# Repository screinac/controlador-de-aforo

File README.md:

# **Sistema Controlador de Aforo**

## Autores
- Oscar Leonardo Riveros Perez
- Sergio Camilo Reina Cardenas

Este repositorio de codigo esta destinado al desarrollo del proyecto de la asignatura Sistemas Embebidos de modo que a continuacion se mostrara todas las consideraciones, guias de diseño, codigo y pruebas para realizar el sistema de control de aforo planteado a continuacion.

## En que consiste el Controlador de Aforo?

El dispositivo consiste en un sistema embebido capaz de detectar la entrada y salida de personas (incluso objetos) de modo que cuenta el aforo aproximado dentro del establecimiento, por lo cual a traves de esta informacion y datos previamente configurados como el area del recinto se pueda obtener cuantas personas ocupan un espacio en el recinto. Ubicando dicha cantidad de personas en 3 zonas (Aforo Libre - Aforo Concurrido - Aforo Lleno) se obtiene un control del estado de aforo del recinto de modo que dependiendo de la zona en la que se encuentre el recinto se emitiran distintas alertas que indican las acciones pertinentes a realizar para evitar el contagio de virus tales como el SARS-CoV-2 entre otros...

 la informacion mostrada y sensada se guarda en un respectivo positivo de almacenamiento para tener los ultimos registros actualizados y otorgar la posibilidad de actualizar el sistema sin necesidad de intervencion con el microcontrolador, ademas de que se implemento una interfaz con un servidor WEB la cual cumple la misma funcion teniendo la posibilidad de configurar el dispositivo y mostrando los datos de aforo en tiempo real.

## Componentes - Controlador de Aforo

El controlador de Aforo cuenta con los siguientes componentes para su funcionamiento:

- Dispositivos Base:
    - ESP32-WROOM-32 -> Microcontrolador
    - HC-SR04 -> Sensor de Distancia
    - Socket MicroSD -> Lector de tarjeta microSD
    - Botones -> Control manual
    - WS2812B -> Led Indicador de zonas
    - Display 7 segmentos (con Integrado TM1637) -> Contador de personas
    - Max98357A -> Amplificador y decodificador I2S
    - Speaker 4 Ohm 3W -> Indicador por Audio
    - Bateria 3.3v

<br /> 

- Alimentacion del dispositivo:
    - USB-C socket -> Puerto de carga
    - TP4056 -> Cargador de Baterias
    - DW01A -> Proteccion Bateria
    - NTF6P02T3G (PMOS) -> Puente de carga
    - MT3608 -> Elevador de tension
    - AMS1117-3v3 -> Regulador de tension 

<br /> 

- Programacion Externa:
    - FT232RL o CP2102

## Funcionalidades

El controlador de aforo ejecuta las siguientes funciones especificas necesarias para el correcto funcionamiento del sistema embebido:

- Leer y Almacener archivos en la memoria MicroSD
- Ejecutar interrupciones Externas
- Conectarse a una red de Wifi
- Enviar bytes de audio a traves del protocolo I2C
- Medir la distancia del entorno
- Cambiar el color de un LED RGB
- Enviar informacion a traves del protocolo especifico TM1637
- Enviar y recibir informacion de un servidor a traves de Wifi
- Carga de bateria a traves de alimentacion USB-C

<br /> 

# **Diseño de la PCB**

La PCB donde va montado el sistema completo del controlador de aforo se divide principalmente en 3 etapas, la primera consiste en la etapa de alimentacion basica para poder suministrar la potencia necesaria tanto a la ESP32 como a los dispositivos externos que posee el controlador de aforo necesarios para su correcto funcionamiento, la segunda etapa consta de el sistema basico que permite programar el microcontrolador para que pueda realizar las funciones requeridas por el usuario y por ultimo la tercera etapa consiste en la implementacion de todos los dispositivos externos que la ESP32 debera gestionar y coordinar correctamente para montar el dispositivo.

## **ESP32-WROOM:**

El microcontrolador que se planteo implementar para el desarrollo del controlador de aforo corresponde al SoC ESP32 debido a que posee integrado un chip capaz de gestionar y conectarse a redes WIFI de modo que dependiendo del establecimiento se pueden sincronizar mas o unos dispositivos a un servidor para su respectiva medicion estimada del flujo de personas en el recinto. 

Es necesario conocer el datasheet respectivo del dispositivo para conocer tanto sus ventajas como las limitaciones del dispositivo, por ende para diseño es importante conocer que el consumo maximo del Chip es de 260mA lo cual implica que es un chip de bajo consumo lo cual abre la posibilidad de poder ser alimentado a traves de baterias.

El esquema de conexiones respectivos del ESP32 se puede encontrar en la imagen a continuacion.

<br /> 

## **Etapa de Alimentacion**

Para la etapa de alimentacion se planteo que el dispositivo deberia ser lo suficientemente portable para poderse implementar en cualquier pared sin necesidad de depender de un tomacorriente, por lo cual se dispuso de la implementacion de una alimentacion hibrida entre una bateria de litio recagable a 3.7v y un puerto USB-C que proveaa la alimentacion necesaria tanto para el dispositivo como para cargar la bateria, por lo cual el primer modulo a plantear corresponde al modulo de carga y proteccion de la bateria.

### **Alimentacion - Modulo de Carga y proteccion de la bateria:**

Para el modulo de carga se ideo extraer la energia necesaria a traves de un conector Tipo-C que se conectase a una fuente de alimentacion, de modo que utilizando el integrado TP4056 con una resistencia de ajuste de valor $1.2k\Omega$ se obtenga una etapa de corriente maxima a 1A aproximadamente y luego una etapa de tension constante para terminar de cargar la bateria, el estado de carga se indicara a traves de 2 LEDs distintos para saber si se encuentra en el proceso de carga o esta terminada la carga de la bateria. Seguido a la etapa de carga se implemento directamente una etapa de proteccion utilizando el integrado DW01A-G el cual protege la bateria de Sobrecarga, Sobredescarga y Cortocircuitos utilizando el circuito de referencia que proporciona el fabricante, de modo que el esquema del Modulo de carga resultante se puede observar en la figura a continuacion:

### **Alimentacion - Puente de Carga**

Es importante tener en cuenta que cuando el circuito se encuentre cargando es necesario aislar la bateria para evitar afectar el proceso de carga de la misma llegando incluso a descargarla si la corriente requerida es mayor que la que se puede suministrar con el modulo de carga, por esto mismo se realizo un puente que cambia entre la conexion de la bateria y la fuente de alimentacion del USB-C a traves de un Mosfet y un diodo schottky lo cual permite que el circuito pueda cargar la bateria al mismo tiempo que seguir en funcionamiento, la unica implicacion a tener en cuenta es que la fuente de alimentacion debe ser capaz de suministrar la corriente de operacion del circuito y la corriente de carga de la bateria para poder funcionar correctamente, el esquema del puente realizado se puede observar en la figura a continuacion:

### **Alimentacion - Multiplicador de Tension:**

Una vez implementado el puente de carga que selecciona entre la bateria o la fuente de alimentacion directa se realizo una etapa de multiplicacion de tension a traves del integrado MT3608 el cual independientemente de la tension de entrada utiliza un sistema de realimentacion para ajustar su salida a 5v, esta etapa se realiza con el fin de poder suministrar la potencia necesaria a aquellos dispositivos que requieren una alimentacion de 5v tales como los modulos HC-SR04 (Ultrasonido) o el integrado MAX98357A (Audio), las resistencias implementadas para conseguir la relacion lineal de realimentacion que proporciona el fabricante corresponden a respectivamente corresponden a R1=$7.5k\Omega$ y R2=$1k\Omega$, su esquema respectivo se puede observar en la siguiente figura:

### **Alimentacion - Regulador de Tension**
Por ultimo se implemento una etapa de regulacion de tension para los dispositivos que lo requieren tales como el ESP32, la tarjeta Micro-SD y el display 7 segmentos respectivamente los cuales no requieren de mucha corriente, por lo cual se utilizo el integrado AMS1117-3.3 que viene previamente calibrado para regular la tension a 3.3v respectivamente facilitando enormemente su esquema de conexion el cual se puede observar en la siguiente figura:

<br />

## **Etapa de Programacion:**

La programacion del dispositivo se realiza a traves de los pines <sub>U0</sub>TXD (41) y <sub>U0</sub>RXD (40) del microcontrolador a traves de la interfaz UART, de modo que se requiere de un dispositivo externo con el cual se pueda realizar la conversion de Serial(USB) a Uart para su programacion respectiva utilizando un computador, en este caso se hara uso del modulo **FT232RL** o **CP2102** de manera externa debido a que la etapa de programacion unicamente se implementa para configurar el microcontrolador.

Para poder implementar el proyecto dentro del microcontrolador se hara uso de la herramienta **ESPTOOL** la cual nos permite flashear(Reescribir) la memoria flash con la aplicacion que se ha programado para el chip, esto haciendo uso de los pines <sub>CLK</sub>OUT1 (23) para reescribir los datos de la memoria y <sub>Chip</sub>PU (9) para reiniciar el microcontrolador.

Arbitrariamente se implemento un led Azul haciendo uso del pin <sub>GPIO</sub>2 de modo que este indique si el dispositivo esta en funcionamiento.

Teniendo en cuenta lo anterior se realizaron las conexiones correspondientes al bloque de la programacion, en el caso de los pines <sub>U0</sub>TXD (41) y <sub>U0</sub>RXD (40) se realizaron conexiones basicas con pines Hembra dejando las conexiones abiertas para cuando se requiera programar el dispositivo, para el pin <sub>CLK</sub>OUT1 (23) se conecto el pin directamente a un boton conectado a tierra debido a que el fabricante especifica que internamente existe una resistencia de Pull-Down por lo cual, al pulsar el boton se entre al Bootloader cuando se requiera, luego para el pin <sub>Chip</sub>PU (9) se realizo una conexion de resistencia Pull-Up con la fuente y tierra usando una resistencia de 10k de modo que cuando se realize una pulsacion se reinicie el dispositivo, por ultimo el LED se conecto al pin <sub>GPIO</sub>2 (22) y a una resistencia de 180 $\Omega$ que va a tierra de modo que se tiene un consumo promedio de 3.3mA, el esquema resultante se puede observar en la siguiente figura:

<br /> 

## **Etapa de Dispositivos Externos**

### **Sistema de Deteccion - Sensor HC-SR04:**

Para el sistema de deteccion se buscaron multiples alternativas que hiciesen posible medir la distancia de un objeto respecto al sensor de modo que finalmente se decidio utilizar el sensor HC-SR04 (Sensor de distancias por Ultrasonido), el sensor HC-SR04 consta de 4 pines siendo estos: Alimentacion(5v), Tierra(GND), Trigger(TTL)-Input y Echo(TTL)-Output de modo que aunque la alimentacion del sensor sea de 5v, la salida de Echo se entrega respecto al nivel TTL de Trigger, por ende se puede implementar directamente sin utilizar conversores logicos 5v-3.3v en el ESP32, adicionalmente se especifica que el sensor consume aproximadamente 15mA de corriente.

Para lograr el sistema de deteccion se penso en implementar hasta 4 sensores ultrasonido de modo que se pudieran implementar multiples configuraciones como se especificara en la programacion respectiva, la implementacion de 4 sensores maximo tiene como consecuencia un consumo maximo de 60mA y el uso de 8 pines logicos en el microcontrolador los cuales estan asignados de la siguiente manera (Trigger, Echo): Ultrasonido 1 (<sub>GPIO</sub>26, <sub>GPIO</sub>36), Ultrasonido 2 (<sub>GPIO</sub>25, <sub>GPIO</sub>39), Ultrasonido 3 (<sub>GPIO</sub>33, <sub>GPIO</sub>34), Ultrasonido 4 (<sub>GPIO</sub>32, <sub>GPIO</sub>35), esta de mas aclarar que estos pines estan conectados directamente a puertos hembra que saldran del empaquetado 3D debido a que el ultrasonido se debe instalar en alguna superficie externa a la placa, el esquema resultante de las conexiones se  observar en la siguiente figura:

<br /> 

### **Control Manual - Botones:**

El sistema de control manual unicamente se basa en la interaccion fisica directa entre algun operario y el mismo sistema, de modo que se implementaron 3 sistemas de resistencias Pull-Up con la fuente y tierra usando resistencias de 10k, ademas de que las conexiones de los botones respectivos se dejo abierta por dos pines hembra debido a que se realizara un cableado para colocar estos botones en la carcasa de la caja, los pines utilizados en el microcontrolador son: <sub>GPIO</sub>27, <sub>GPIO</sub>14 y <sub>GPIO</sub>12, el esquema resultante del control manual se puede observar en la figura a continuacion:

<br /> 

### **Sistema de Indicadores:**

En este apartado se implementaron distintos metodos para tener una interaccion mas directa desde el sistema con el usuario, por lo cual a continuacion se describiran los multiples sistemas implementados para dar indicaciones a los usuarios.

#### **Sistema de Indicadores - Audio:**

En el caso del Sistema Indicador de Audio se vieron diferentes formas de implementar un speaker, de modo que se opto por implementar el integrado MAX98357A el cual consiste en un decodificador del protocolo I2S seguido de un DAC interno con una etapa de amplificacion clase D. Para el proposito del proyecto aunque el protocolo soportase usar dos canales diferentes, unicamente se implemento un canal (Izquierdo) lo cual implica que el pin SD_MODE del integrado esta conectado directamente a 3.3v, adicionalmente se escogio de manera arbitraria obtener una amplificacion de 15dB por lo cual como se especifica en su datasheet se conecto el pin de ganancia a tierra mediante una resistencia de 100k $\Omega$, otras consideraciones que se realizaron es que las salidas del Speaker (R+ y R-) se conectaron en serie con una impedancia dinamica de altas frecuencias junto a condensadores para filtrar el ruido de alta frecuencia que se puede encontrar el altavoz. Con lo anterior en cuenta se utilizaron 3 pines del microcontrolador destinados al protocolo I2S siendo estos <sub>GPIO</sub>21 (Serial Clock), <sub>GPIO</sub>22 (LRCLK) y <sub>GPIO</sub>19 (Data In), es importante tener en cuenta que el integrado esta diseñado para altavoces entre 4 $\Omega$ y 8 $\Omega$ ademas de tener una entrada de alimentacion entre 2.5v y 5v, lo cual implica que la potencia maxima de la amplificacion es de 3.2w y por ende entrega una corriente maxima de 1.25A, el esquema resultante se puede ver en la figura a continuacion:

#### **Sistema de Indicadores - LEDs:**
Para el sistema de Indicador visual de LEDs se planteo la utilizacion de los LEDs 
WS2812B que funcionan a traves de señales digitales y permiten el acople de multiples LEDs utilizando la misma linea de datos de modo que se utilizo el pin <sub>GPIO</sub>23 del microcontrolador para su respectivo control, originalmente se plantea implementar un unico LED RGB pero no se descarta la opcion de implementar LEDs adicionales, de modo que se crea una segunda conexion para realizar el acople con uno o mas LEDs adicionales ademas se debe tener en cuenta que el consumo maximo de cada LED es de 50mA (16mA por cada subLED), debido a que se planea montar los LEDs en la carcasa del dispositivo se realizaron conexiones hembra para todos los pines tanto del primer LED como el acople con los LEDs adicionales para cablearlos afuera de la placa, el esquema respectivo se puede observar en la siguiente figura:

<br /> 

### **Sistema de Almacenamiento - MicroSD:**

En el sistema de almacenamiento se opto por la implementacion de una tarjeta Micro-SD a traves del protocolo de comunicacion SPI, de modo que se utilizan 4 pines del microcontrolador siento estos <sub>GPIO</sub>17 (SD_Clock), <sub>GPIO</sub>5 (SD_Input), <sub>GPIO</sub>16 (SD_Output) y <sub>GPIO</sub>18 (Chip Select), la tarjeta MicroSD se conecto a traves de su socket respectivo de modo que se ha de tener en cuenta que esta consume aproximadamente 50mA cuando opera a traves del protocolo SPI, adicionalmente se conecto un LED azul en el Socket de la tarjeta con una resistencia de 180 $\Omega$, el cual funciona como indicador de cuando esta conectada la tarjeta o desconectada de modo que genera un consumo adicional de 3.3mA, el diagrama de conexiones del sistema de almacenamiento se puede observar a continuacion:

<br /> 

### **Puertos de Expansion - ${I^2C}$ y GPIO:** 

Debido a que unicamente sobran 3 pines del microcontrolador se decidio conectar 2 de ellos a traves del protocolo de comunicacion ${I^2C}$ de modo que se conectaron en un sistema resistor de Pull-Up con una resistencia de 5k $\Omega$ a la fuente y se dejaron sus conexiones libres a pines hembra para poder conectar dispositivos adicionales con este sistema, los pines implementados para el $I^2C$ Corresponden a <sub>GPIO</sub>15 (SCL) y <sub>GPIO</sub>13 (SDA). En el caso del ultimo pin libre el cual es <sub>GPIO</sub>4 se creo una conexion a un pin hembra de modo que en caso que se requiera por alguna funcionalidad adicional se pueda utilizar libremente en la placa, el esquema correspondiente de los puertos de expansion se pueden observar en la siguiente figura:

<br /> 

### **Esquema General - ESP32:** 

El esquema general de las conexiones anteriormente mencionadas al microcontrolador se puede observar en la figura a continuacion:

<br />

## **PCB y Modelo-3D**

Una vez descritas todas las conexiones planteadas y las funcionalidades de la placa se realizo el respectivo ruteo de las pistas en la PCB teniendo en cuenta las corrientes maximas que se deben soportar sobre cada pista cuando el dispositivo bajo maxima operacion y cargando la bateria respectivamente (Se estima que maximo se consuman hasta 2.6A en casos extremos por la pista VBus), adicionalmente se tomo el tiempo necesario para realizar todas las pistas sobre la capa superior de la placa dando como resultado los esquemas que se observaran a continuacion:

Teniendo el diseño completo de la PCB del controlador de aforo se utilizaron distintos servicios para fabricar y soldar el sistema completo obteniendose la placa que se puede observar en las siguientes imagenes:

Ahora, con el el fin de unicamente de tener el dispositivo empaquetado con los elementos con los que el usuario interactua visibles, se realizo una caja sencilla con las aperturas necesarias de modo que se pudiese ingresar el dispositivo dentro de ella, tal y como se puede observar a continuacion.

# **Programacion del Dispositivo**

Una vez realizado el diseño y fabricacion de la PCB donde se  integran los componentes necesarios para el correcto funcionamiento tanto del microcontrolador como los dispositivos externos, se realiza la respectiva programacion del microcontrolador a traves de micropython. El desarrollo del codigo necesario para controlar los perisfericos individualmente se presenta a continuacion:

- [Display 7 Segmentos - TM1637](/Perifericos/7segmentos.md)

- [LED RGB - WS2812B](/Perifericos/LEDRGB.md)

- [Botones - Interrupciones](/Perifericos/Botones.md)

- [Ultrasonido - HC-SR04](/Perifericos/Ultrasonido.md)

- [Almacenamiento - MicroSD](/Perifericos/MicroSD.md)

- [Audio - MAX98357A](/Perifericos/Audio.md)

Una vez realizado el codigo necesario para controlar los diferentes perifericos para el controlador de aforo, se implemento el codigo principal del sistema el cual se puede resumir en el siguiente diagrama donde se muestra la logica del algoritmo de ejecucion. 

De modo que teniendo la rutina de funcionamiento del sistema controlador de aforo se pone a prueba su funcionamiento tal y como se puede observar en los siguientes videos

[Video Prueba Codigo Principal](https://drive.google.com/file/d/1DpC-rx6eNb7NdOsbPi9TDKSZAz35STaH/view?usp=sharing "Video Prueba Codigo Principal")

[Video Prueba Codigo Principal - Botones](https://drive.google.com/file/d/1Xm1BT4d_Bo_UqYZqokCm6PzdpIdTOp7b/view?usp=sharing "Video Prueba Codigo Principal - Botones")

[Controlador de Aforo - Prueba #1](https://drive.google.com/file/d/15uGaQDlrFzsJZFsqkCuU1Zft-tO57118/view?usp=sharing "Controlador de Aforo - Prueba #1")

[Controlador de Aforo - Prueba #2](https://drive.google.com/file/d/1f2GRTZBahxgxNUtWcc2ShW_QZQ9_Vtpt/view?usp=sharing "Controlador de Aforo - Prueba #2")

</br>

## **Notas de Diseño**

Algo que se debe tener muy en cuenta a la hora de replicar el controlador de aforo para mejorar el diseño corresponde a las resistencias Pull-Up implementadas en los botones, esto debido a que no se observo que en el datasheet del microcontrolador implementado se especifica que el Pin 12 debe estar en configuracion Pull-Down para el correcto funcionamiento de la placa, en este caso debido a que se implemento una resistencia Pull-Up la placa generaba error al intentar ser programada por lo cual se tuvo que quitar el resistor correspondiente al pin GPIO12 para deshabilitar el respectivo Pull-UP, la tabla que especifica si un pin debe estar en configuracion Pull-Up o Pull-Down para su correcto funcionamiento al reiniciar es la siguiente:

Adicionalmente no se contaba con que se necesitarian mas puertos de alimentacion de 3.3v por lo cual se deben generar 4 pines de alimentacion de 3.3v para alimentar diferentes dispositivos.

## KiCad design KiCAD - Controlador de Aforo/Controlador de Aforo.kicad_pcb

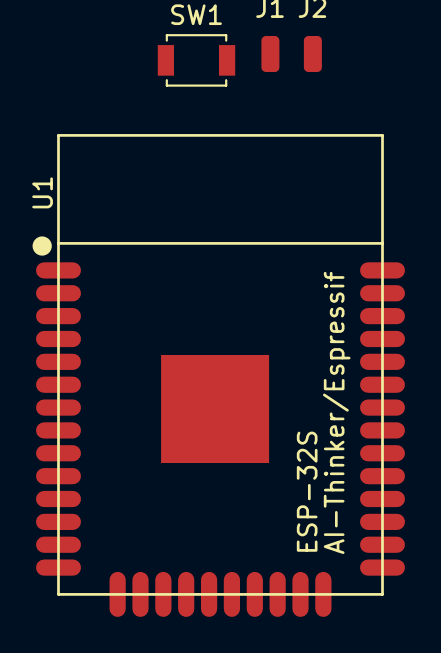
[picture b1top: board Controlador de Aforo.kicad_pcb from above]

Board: 2 copper layers, 4 parts (0 on the bottom side), 4 nets, no tracks yet.

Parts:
J1, J2: Conn_01x01_Female; SolderWirePad_1x01_SMD_1x2mm
SW1: SW_Push; SW_SPST_B3U-1000P
U1: ESP-32S

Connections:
/Programador/Boot-Flash: SW1.1, U1.25
/Programador/Ground: SW1.2, U1.38
/Programador/RXDu0: J1.1, U1.34
/Programador/TXDu0: J2.1, U1.35

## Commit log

2021-10-21 se agregan la idea 11 y 12
2021-11-04 esquema
2021-11-04 esquema profe
2021-11-04 notas
2021-11-04 Update Notas-y-presupuesto
2021-11-04 infrarojo eliminado
2021-11-09 cambios esquema
2021-11-11 kicad
2021-11-16 Base
2021-11-16 Adicion de Imagen
2021-11-17 Actualizacion ESP32
2021-11-23 kicad alimentacion
2021-12-26 Actualizacion Documentacion - Diseño Esquematico
2021-12-27 Esquematico Completo - Documentacion Diseño
2021-12-27 Datasheet - Modulos
2022-01-13 Seccion PCB
2022-01-18 software
2022-01-24 Inicio de Programacion
2022-01-24 Actualizacion Imagenes
2022-01-25 main code init
2022-01-26 ModuloMicroSD
2022-01-26 Libreria Audio
2022-01-26 CambiosLoop
2022-01-26 Documentacion modulo de Audio
2022-01-27 Adicion y pruebas, WS2812, Ultrasonido y 7segmento
2022-01-27 Documentacion WS2812 y 7segmentos
2022-01-27 Documentacion Ultrasonido
2022-01-27 Documentacion botones y pruebas modulo WIFI
2022-02-02 Codigo Principal
2022-02-02 Main Code sin Wifi
2022-02-02 copia de seguridad configuracion
2022-02-03 Actualizacion 1.0001
2022-02-03 Actualizacion Documentacion - Funcionalidades
2022-02-06 Actualizacion documentacion - Diseño
2022-02-06 Actualizacion Documentacion - 7 segmentos
2022-02-06 Actualizacion Documentacion - Botones
2022-02-06 Actualizacion Documentacion - Modulo Ultrasonido
2022-02-06 Actualizacion Documentacion-Ultradoc MicroSD
2022-02-07 Actualizacion Documentacion - Audio
2022-02-07 Actualizacion Main
2022-02-07 Actualizacion Doc - Codigo Principal y videos
2022-02-07 Actualizacion - Diagramas originales Krita
2022-02-09 Actualizacion Documentacion
2022-02-09 Main - 2 ultrasonidos
2022-02-10 Actualizacion
2022-02-10 Actualizacion Documentacion FInal
2022-02-10 Bateria Cargando
